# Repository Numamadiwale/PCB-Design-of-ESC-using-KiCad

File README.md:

# PCB-Design-of-ESC-using-KiCad
PCB Reverse Engineered Design of an ESC using Kicad ver 9.0
This design is Reverse Engineered design of hakrc 4255 120a single ESC however this design isnt a 100% recreation of the original Design and liberties were taken while designing the device. the design is yet to be Validated by a seasoned PCB designer before it can be considered for production

The Design had no DRC Errors but had "floating island" warnings , take this into strict considerations before attempting anything. Design optimization is highly needed to further minimize the size of the board

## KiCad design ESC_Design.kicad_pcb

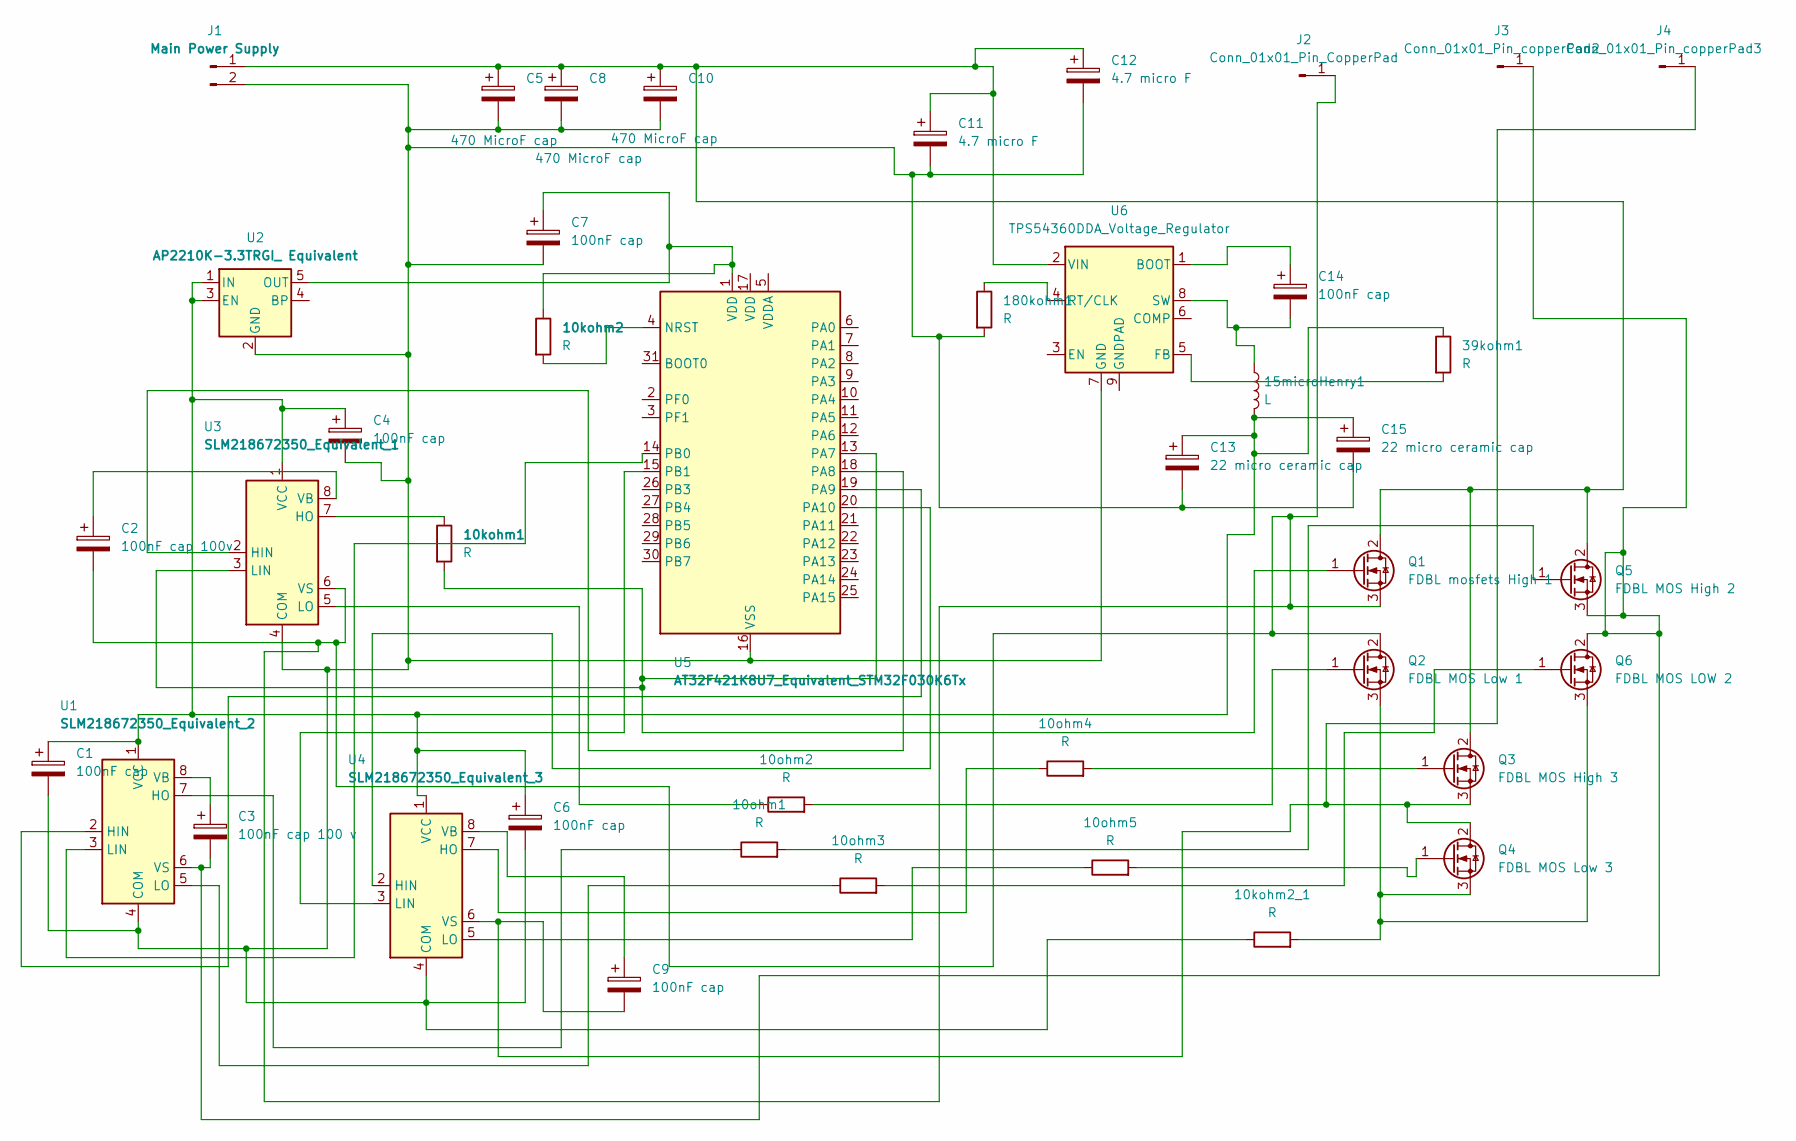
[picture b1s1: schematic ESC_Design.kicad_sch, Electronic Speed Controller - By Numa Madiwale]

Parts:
10kohm1, 10kohm2, 10kohm2_1, 10ohm1, 10ohm2, 10ohm3, 10ohm4, 10ohm5, 39kohm1, 180kohm1: R; R_0603_1608Metric
15microHenry1: L; L_12x12mm_H8mm
C1, C4, C6, C7, C9, C14: 100nF cap; C_0805_2012Metric
C2: 100nF cap 100v; C_0805_2012Metric
C3: 100nF cap 100 v; C_0805_2012Metric
C5, C8, C10: 470 MicroF cap; C_0805_2012Metric
C11, C12: 4.7 micro F; C_0805_2012Metric
C13, C15: 22 micro ceramic cap; C_1210_3225Metric
J1: Main Power Supply; AMASS_XT60-M_1x02_P7.20mm_Vertical
J2: Conn_01x01_Pin_CopperPad; TestPoint_Pad_4.0x4.0mm
J3: Conn_01x01_Pin_copperPad2; TestPoint_Pad_4.0x4.0mm
J4: Conn_01x01_Pin_copperPad3; TestPoint_Pad_4.0x4.0mm
Q1: FDBL mosfets High 1; TO-263-7_TabPin8
Q2: FDBL MOS Low 1; TO-263-7_TabPin8
Q3: FDBL MOS High 3; TO-263-7_TabPin8
Q4: FDBL MOS Low 3; TO-263-7_TabPin8
Q5: FDBL MOS High 2; TO-263-7_TabPin8
Q6: FDBL MOS LOW 2; TO-263-7_TabPin8
U1: SLM218672350_Equivalent_2; SOIC-8_3.9x4.9mm_P1.27mm
U2: AP2210K-3.3TRGI_ Equivalent; SOT-23-5
U3: SLM218672350_Equivalent_1; SOIC-8_3.9x4.9mm_P1.27mm
U4: SLM218672350_Equivalent_3; SOIC-8_3.9x4.9mm_P1.27mm
U5: AT32F421K8U7_Equivalent_STM32F030K6Tx; LQFP-32_7x7mm_P0.8mm
U6: TPS54360DDA_Voltage_Regulator; SOIC-8-1EP_3.9x4.9mm_P1.27mm_EP2.29x3mm_ThermalVias

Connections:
unnamed: C5.1, C8.1, C10.1, C11.1, C12.1, J1.1, Q1.2 (D), Q3.2 (D), Q5.2 (D), U6.2 (VIN)
unnamed: 10kohm2_1.1, 180kohm1.2, C1.2, C4.2, C5.2, C6.2, C7.2, C8.2, C10.2, C11.2, C12.2, C13.2, C15.2, J1.2, U1.4 (COM), U2.2 (GND), U3.4 (COM), U4.4 (COM), U5.16 (VSS), U5.32 (VSS), U6.7 (GND)
unnamed: C2.2, J2.1, Q1.3 (S), Q2.2 (D), U3.6 (VS)
unnamed: C3.2, J3.1, Q5.3 (S), Q6.2 (D), U1.6 (VS)
unnamed: C9.2, J4.1, Q3.3 (S), Q4.2 (D), U4.6 (VS)
unnamed: 10kohm1.2, Q1.1 (G), U3.3 (LIN), U5.13 (PA7)
unnamed: 10ohm2.2, Q2.1 (G)
unnamed: 10kohm2_1.2, Q2.3 (S), Q4.3 (S), Q6.3 (S)
unnamed: 10ohm4.2, Q3.1 (G)
unnamed: 10ohm5.2, Q4.1 (G)
unnamed: 10ohm1.2, Q5.1 (G)
unnamed: 10ohm3.2, Q6.1 (G)
unnamed: U1.2 (HIN), U5.19 (PA9)
unnamed: 10ohm1.1, U1.7 (HO)
unnamed: U1.3 (LIN), U5.14 (PB0)
unnamed: 10ohm3.1, U1.5 (LO)
unnamed: C3.1, U1.8 (VB)
unnamed: 15microHenry1.2, 39kohm1.1, C1.1, C4.1, C6.1, C13.1, C15.1, U1.1 (VCC), U2.1 (IN), U2.3 (EN), U3.1 (VCC), U4.1 (VCC)
unnamed: 10kohm2.1, C7.1, U2.5 (OUT), U5.1 (VDD)
unnamed: U3.2 (HIN), U5.18 (PA8)
unnamed: 10kohm1.1, U3.7 (HO)
unnamed: 10ohm2.1, U3.5 (LO)
unnamed: C2.1, U3.8 (VB)
unnamed: U4.2 (HIN), U5.20 (PA10)
unnamed: 10ohm4.1, U4.7 (HO)
unnamed: U4.3 (LIN), U5.15 (PB1)
unnamed: 10ohm5.1, U4.5 (LO)
unnamed: C9.1, U4.8 (VB)
unnamed: 10kohm2.2, U5.4 (NRST)
unnamed: C14.1, U6.1 (BOOT)
unnamed: 39kohm1.2, U6.5 (FB)
unnamed: 180kohm1.1, U6.4 (RT/CLK)
unnamed: 15microHenry1.1, C14.2, U6.8 (SW)

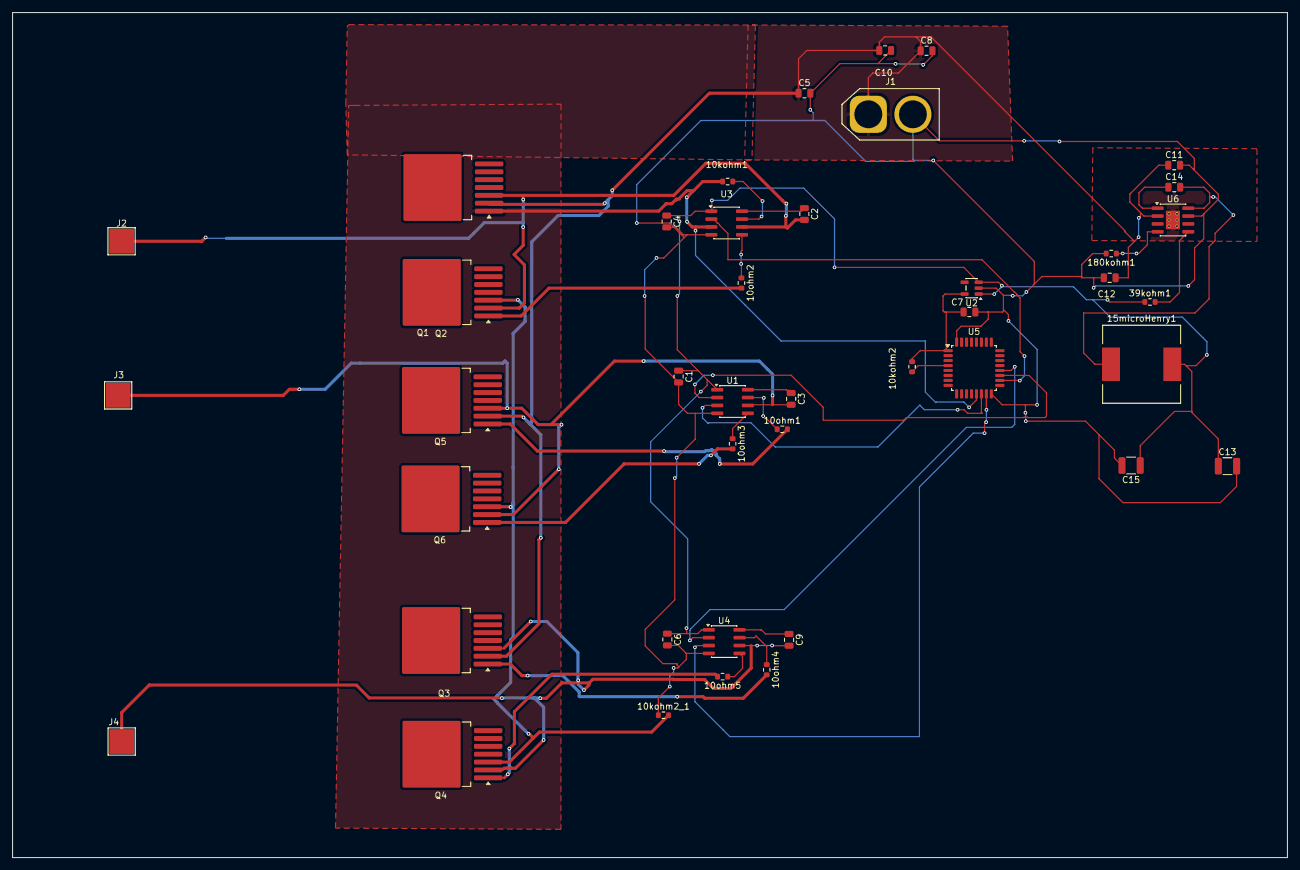
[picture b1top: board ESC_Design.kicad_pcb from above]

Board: 2 copper layers, 205.9 x 136.5 mm, 42 parts (0 on the bottom side), 33 nets.
